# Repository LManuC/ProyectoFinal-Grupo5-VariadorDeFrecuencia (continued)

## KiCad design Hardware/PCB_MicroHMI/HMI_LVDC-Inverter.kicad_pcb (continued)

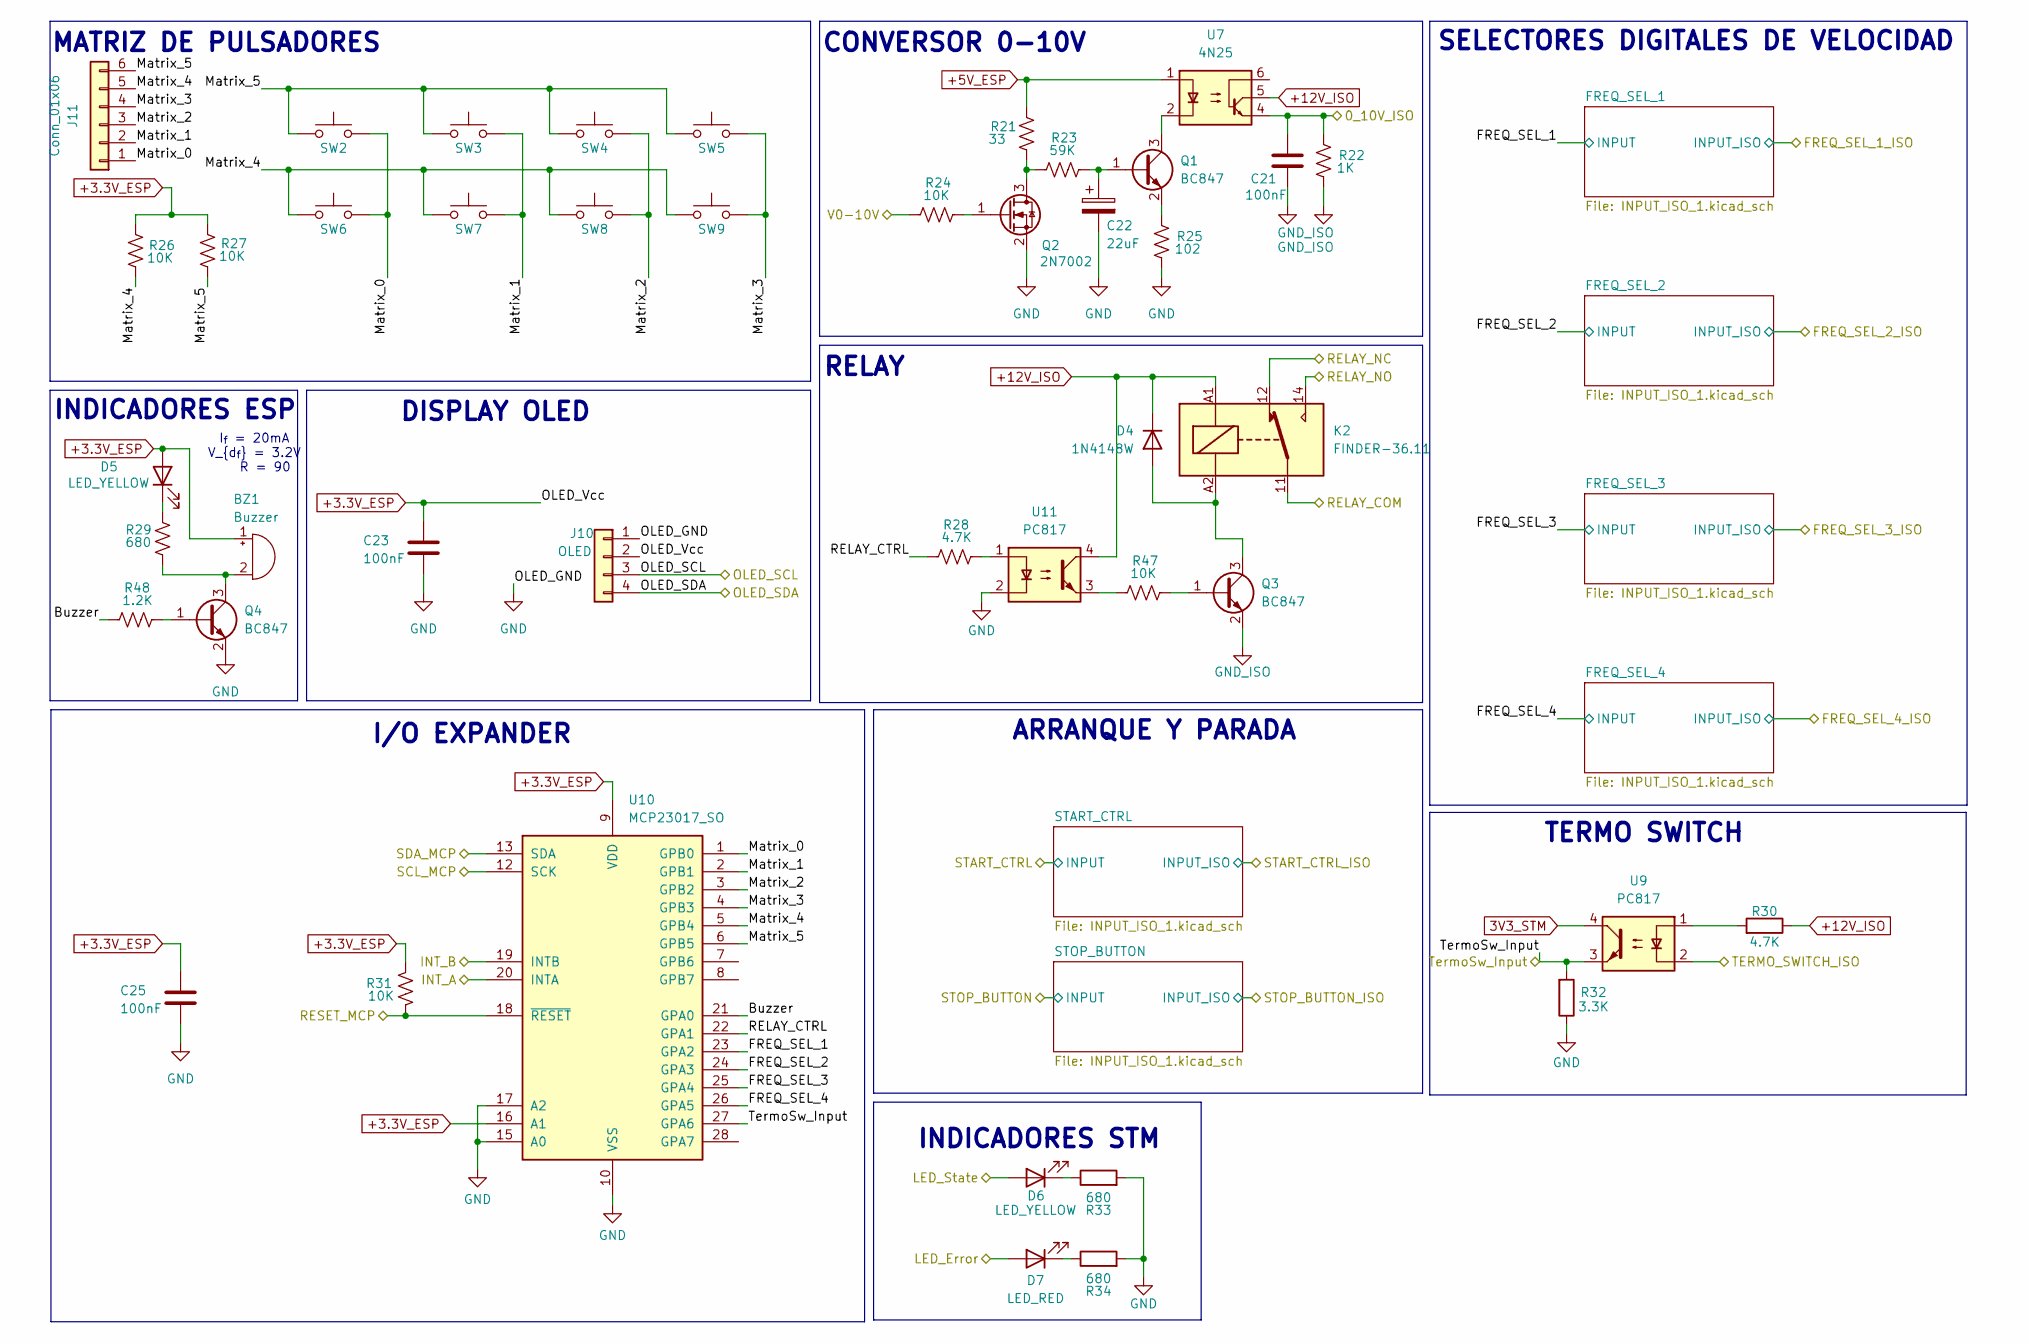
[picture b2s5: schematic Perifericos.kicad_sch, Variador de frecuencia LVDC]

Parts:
BZ1: Buzzer; Buzzer_12x9.5RM7.6
C21, C23, C25: 100nF; C_0603_1608Metric_Pad1.08x0.95mm_HandSolder
C22: 22uF; CP_Elec_5x5.4
D4: 1N4148W; D_SOD-123
D5, D6: LED_YELLOW; LED_0603_1608Metric_Pad1.05x0.95mm_HandSolder
D7: LED_RED; LED_0603_1608Metric_Pad1.05x0.95mm_HandSolder
J10: OLED; PinHeader_1x04_P2.54mm_Horizontal
J11: Conn_01x06; PinHeader_1x06_P2.54mm_Horizontal
K2: FINDER-36.11; Relay_SPDT_Finder_36.11
Q1, Q3, Q4: BC847; SOT-523
Q2: 2N7002; SOT-23
R21: 33; R_1210_3225Metric_Pad1.30x2.65mm_HandSolder
R22: 1K; R_0603_1608Metric_Pad0.98x0.95mm_HandSolder
R23: 59K; R_0603_1608Metric_Pad0.98x0.95mm_HandSolder
R24, R26, R27, R31, R47: 10K; R_0603_1608Metric_Pad0.98x0.95mm_HandSolder
R25: 102; R_0603_1608Metric_Pad0.98x0.95mm_HandSolder
R28, R30: 4.7K; R_0603_1608Metric_Pad0.98x0.95mm_HandSolder
R29, R33, R34: 680; R_0603_1608Metric_Pad0.98x0.95mm_HandSolder
R32: 3.3K; R_0603_1608Metric_Pad0.98x0.95mm_HandSolder
R48: 1.2K; R_0603_1608Metric_Pad0.98x0.95mm_HandSolder
SW2, SW3, SW4, SW5, SW6, SW7, SW8, SW9: SW_MEC_5G; SW_Push_SPST_NO_Alps_SKRK
U7: 4N25; DIP-6_W7.62mm_SMDSocket_SmallPads
U9, U11: PC817; DIP-4_W7.62mm_SMDSocket_SmallPads
U10: MCP23017_SO; SOIC-28W_7.5x17.9mm_P1.27mm

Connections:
3V3_STM: U9.4; also elsewhere on the board
+3.3V_ESP: BZ1.1 (+), C23.1, C25.1, D5.2 (A), J10.2, R26.1, R27.1, R31.1, U10.9 (VDD), U10.16 (A1); also elsewhere on the board
+5V_ESP: R21.2, U7.1; also elsewhere on the board
+12V_ISO: D4.1 (K), K2.A1, R30.1, U7.5, U11.4; also elsewhere on the board
/ESP32/INT_A: U10.20 (INTA); also elsewhere on the board
/ESP32/INT_B: U10.19 (INTB); also elsewhere on the board
/ESP32/OLED_SCL: J10.3; also elsewhere on the board
/ESP32/OLED_SDA: J10.4; also elsewhere on the board
/ESP32/RESET_MCP: R31.2, U10.18 (~RESET); also elsewhere on the board
/ESP32/SCL_MCP: U10.12 (SCK); also elsewhere on the board
/ESP32/SDA_MCP: U10.13 (SDA); also elsewhere on the board
/ESP32/V0-10V: R24.1; also elsewhere on the board
/Perifericos/0_10V_ISO: C21.1, R22.2, U7.4; also elsewhere on the board
/Perifericos/Buzzer: R48.1, U10.21 (GPA0)
/Perifericos/FREQ_SEL_1: U10.23 (GPA2); also elsewhere on the board
/Perifericos/FREQ_SEL_2: U10.24 (GPA3); also elsewhere on the board
/Perifericos/FREQ_SEL_3: U10.25 (GPA4); also elsewhere on the board
/Perifericos/FREQ_SEL_4: U10.26 (GPA5); also elsewhere on the board
/Perifericos/LED_Error: D7.2 (A); also elsewhere on the board
/Perifericos/LED_State: D6.2 (A); also elsewhere on the board
/Perifericos/Matrix_0: J11.1, SW2.2 (B), SW6.2 (B), U10.1 (GPB0)
/Perifericos/Matrix_1: J11.2, SW3.2 (B), SW7.2 (B), U10.2 (GPB1)
/Perifericos/Matrix_2: J11.3, SW4.2 (B), SW8.2 (B), U10.3 (GPB2)
/Perifericos/Matrix_3: J11.4, SW5.2 (B), SW9.2 (B), U10.4 (GPB3)
/Perifericos/Matrix_4: J11.5, R26.2, SW6.1 (A), SW7.1 (A), SW8.1 (A), SW9.1 (A), U10.5 (GPB4)
/Perifericos/Matrix_5: J11.6, R27.2, SW2.1 (A), SW3.1 (A), SW4.1 (A), SW5.1 (A), U10.6 (GPB5)
/Perifericos/RELAY_COM: K2.11; also elsewhere on the board
/Perifericos/RELAY_CTRL: R28.1, U10.22 (GPA1)
/Perifericos/RELAY_NC: K2.12; also elsewhere on the board
/Perifericos/RELAY_NO: K2.14; also elsewhere on the board
/Perifericos/TERMO_SWITCH_ISO: U9.2; also elsewhere on the board
/Perifericos/TermoSw_Input: R32.2, U9.3, U10.27 (GPA6); also elsewhere on the board
GND: C22.2, C23.2, C25.2, J10.1, Q2.2 (S), Q4.2 (E), R25.1, R32.1, R33.2, R34.2, U10.10 (VSS), U10.15 (A0), U10.17 (A2), U11.2; also elsewhere on the board
GND_ISO: C21.2, Q3.2 (E), R22.1; also elsewhere on the board
unnamed: BZ1.2 (-), Q4.3 (C), R29.2
unnamed: D4.2 (A), K2.A2, Q3.3 (C)
unnamed: D5.1 (K), R29.1
unnamed: D6.1 (K), R33.1
unnamed: D7.1 (K), R34.1
unnamed: C22.1, Q1.1 (B), R23.2
unnamed: Q1.3 (C), U7.2
unnamed: Q1.2 (E), R25.2
unnamed: Q2.3 (D), R21.1, R23.1
unnamed: Q2.1 (G), R24.2
unnamed: Q3.1 (B), R47.2
unnamed: Q4.1 (B), R48.2
unnamed: R28.2, U11.1
unnamed: R30.2, U9.1
unnamed: R47.1, U11.3

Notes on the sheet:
R = 90
I_{f} = 20mA V_{d_{f}} = 3.2V
RELAY
MATRIZ DE PULSADORES
ARRANQUE Y PARADA
INDICADORES STM
TERMO SWITCH
I/O EXPANDER
DISPLAY OLED
INDICADORES ESP
SELECTORES DIGITALES DE VELOCIDAD
CONVERSOR 0-10V

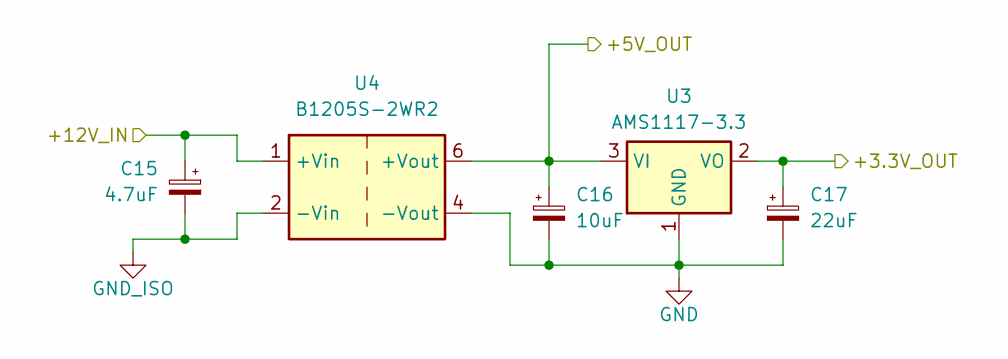
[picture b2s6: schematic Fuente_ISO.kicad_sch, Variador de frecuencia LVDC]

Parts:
C15: 4.7uF; C_0603_1608Metric
C16: 10uF; CP_Elec_4x5.4
C17: 22uF; CP_Elec_4x5.4
U3: AMS1117-3.3; SOT-223-3_TabPin2
U4: B1205S-2WR2; Converter_DCDC_TRACO_TMA-05xxS_12xxS_Single_THT

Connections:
3V3_STM: C17.1, U3.2 (VO); also elsewhere on the board
+12V_ISO: C15.1, U4.1 (+Vin); also elsewhere on the board
/Fuentes/Fuente_ISO/+5V_OUT: C16.1, U3.3 (VI), U4.6 (+Vout)
GND: C16.2, C17.2, U3.1 (GND), U4.4 (-Vout); also elsewhere on the board
GND_ISO: C15.2, U4.2 (-Vin); also elsewhere on the board

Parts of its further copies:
C18: 4.7uF; C_0603_1608Metric
C19: 10uF; CP_Elec_4x5.4
C20: 22uF; CP_Elec_4x5.4
U5: AMS1117-3.3; SOT-223-3_TabPin2
U6: B1205S-2WR2; Converter_DCDC_TRACO_TMA-05xxS_12xxS_Single_THT

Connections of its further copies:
+3.3V_ESP: C20.1, U5.2 (VO); also elsewhere on the board
+5V_ESP: C19.1, U5.3 (VI), U6.6 (+Vout); also elsewhere on the board
+12V_ISO: C18.1, U6.1 (+Vin); also elsewhere on the board
GND: C19.2, C20.2, U5.1 (GND), U6.4 (-Vout); also elsewhere on the board
GND_ISO: C18.2, U6.2 (-Vin); also elsewhere on the board

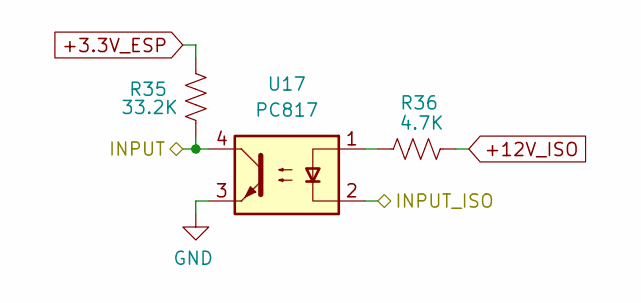
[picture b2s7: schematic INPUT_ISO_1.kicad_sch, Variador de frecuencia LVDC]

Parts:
R35: 33.2K; R_0603_1608Metric_Pad0.98x0.95mm_HandSolder
R36: 4.7K; R_0603_1608Metric_Pad0.98x0.95mm_HandSolder
U17: PC817; DIP-4_W7.62mm_SMDSocket_SmallPads

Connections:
+3.3V_ESP: R35.2; also elsewhere on the board
+12V_ISO: R36.2; also elsewhere on the board
/Perifericos/FREQ_SEL_1: R35.1, U17.4; also elsewhere on the board
/Perifericos/FREQ_SEL_1_ISO: U17.2; also elsewhere on the board
GND: U17.3; also elsewhere on the board
unnamed: R36.1, U17.1

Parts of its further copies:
R37, R39, R41, R43, R45: 33.2K; R_0603_1608Metric_Pad0.98x0.95mm_HandSolder
R38, R40, R42, R44, R46: 4.7K; R_0603_1608Metric_Pad0.98x0.95mm_HandSolder
U18, U19, U20, U21, U22: PC817; DIP-4_W7.62mm_SMDSocket_SmallPads

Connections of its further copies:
+3.3V_ESP: R37.2, R39.2, R41.2, R43.2, R45.2; also elsewhere on the board
+12V_ISO: R38.2, R40.2, R42.2, R44.2, R46.2; also elsewhere on the board
/ESP32/START_CTRL: R43.1, U21.4; also elsewhere on the board
/ESP32/STOP_BUTTON: R45.1, U22.4; also elsewhere on the board
/Perifericos/FREQ_SEL_2: R37.1, U18.4; also elsewhere on the board
/Perifericos/FREQ_SEL_2_ISO: U18.2; also elsewhere on the board
/Perifericos/FREQ_SEL_3: R39.1, U19.4; also elsewhere on the board
/Perifericos/FREQ_SEL_3_ISO: U19.2; also elsewhere on the board
/Perifericos/FREQ_SEL_4: R41.1, U20.4; also elsewhere on the board
/Perifericos/FREQ_SEL_4_ISO: U20.2; also elsewhere on the board
/Perifericos/START_CTRL_ISO: U21.2; also elsewhere on the board
/Perifericos/STOP_BUTTON_ISO: U22.2; also elsewhere on the board
GND: U18.3, U19.3, U20.3, U21.3, U22.3; also elsewhere on the board
unnamed: R38.1, U18.1
unnamed: R40.1, U19.1
unnamed: R42.1, U20.1
unnamed: R44.1, U21.1
unnamed: R46.1, U22.1

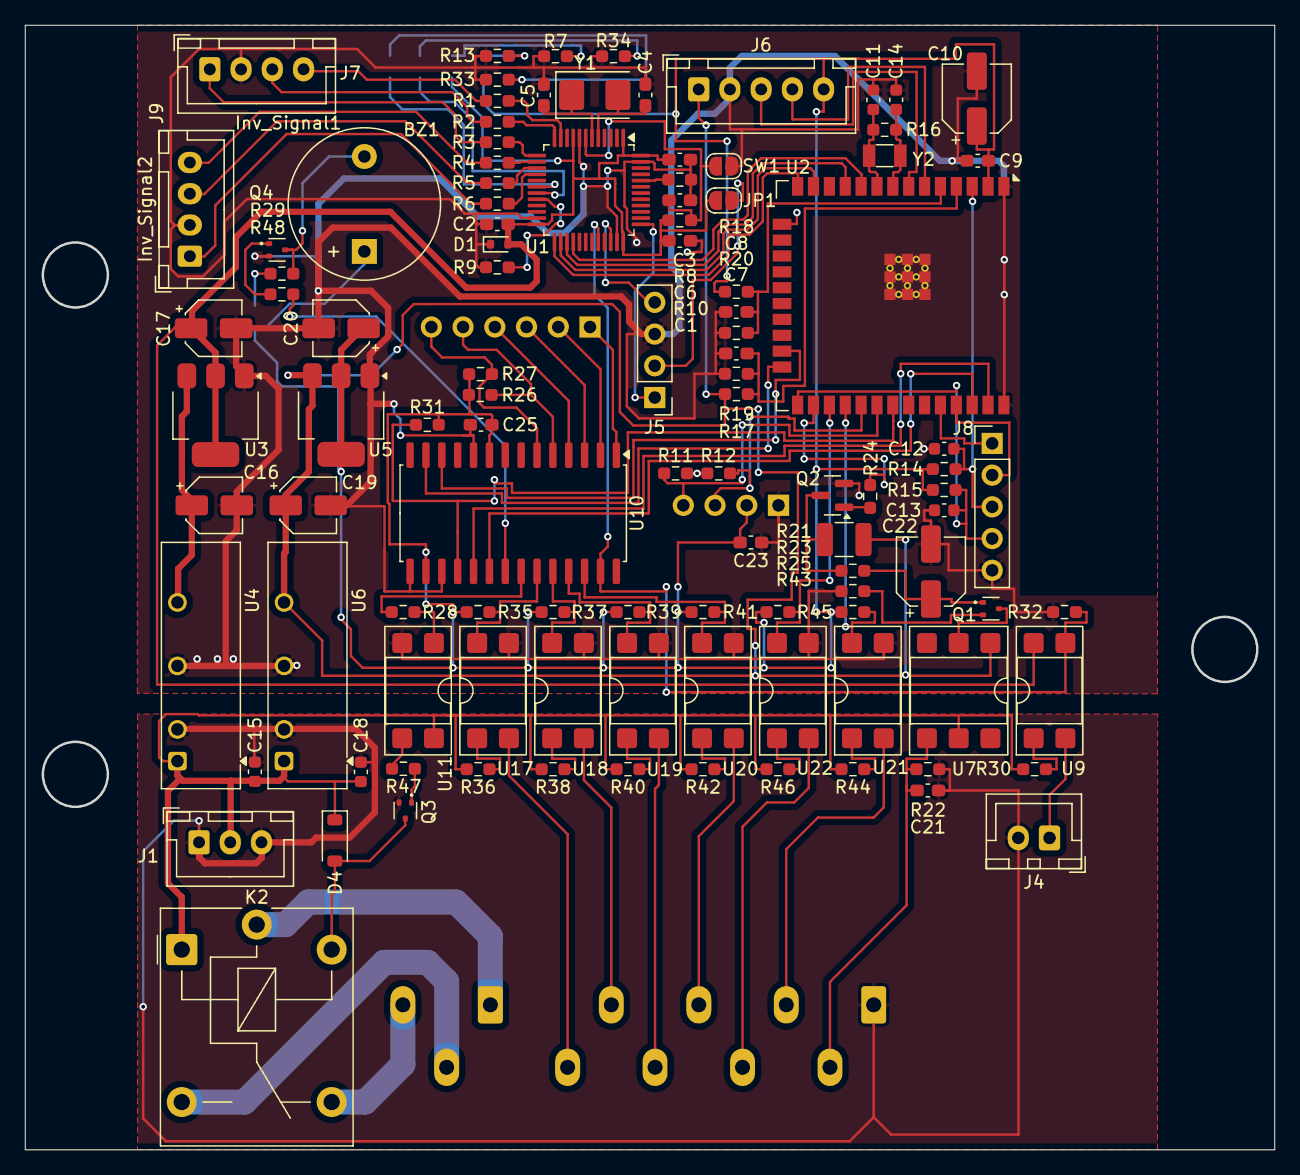
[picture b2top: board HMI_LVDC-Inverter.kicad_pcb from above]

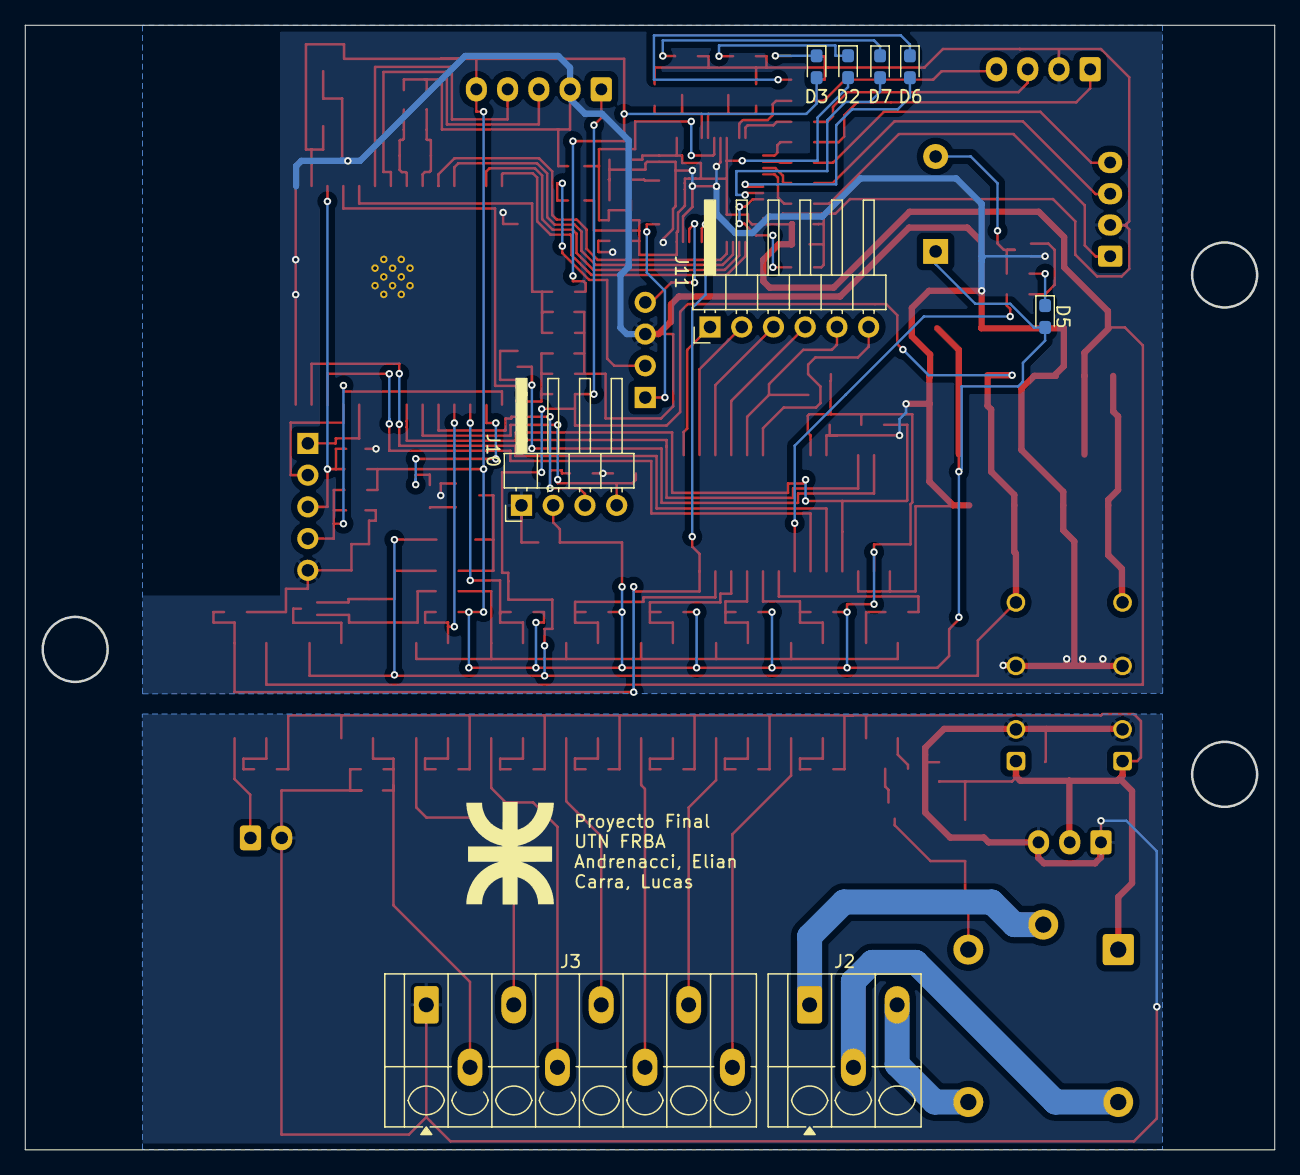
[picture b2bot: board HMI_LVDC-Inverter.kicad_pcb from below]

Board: 2 copper layers, 99.9 x 89.9 mm, 116 parts (9 on the bottom side), 100 nets.

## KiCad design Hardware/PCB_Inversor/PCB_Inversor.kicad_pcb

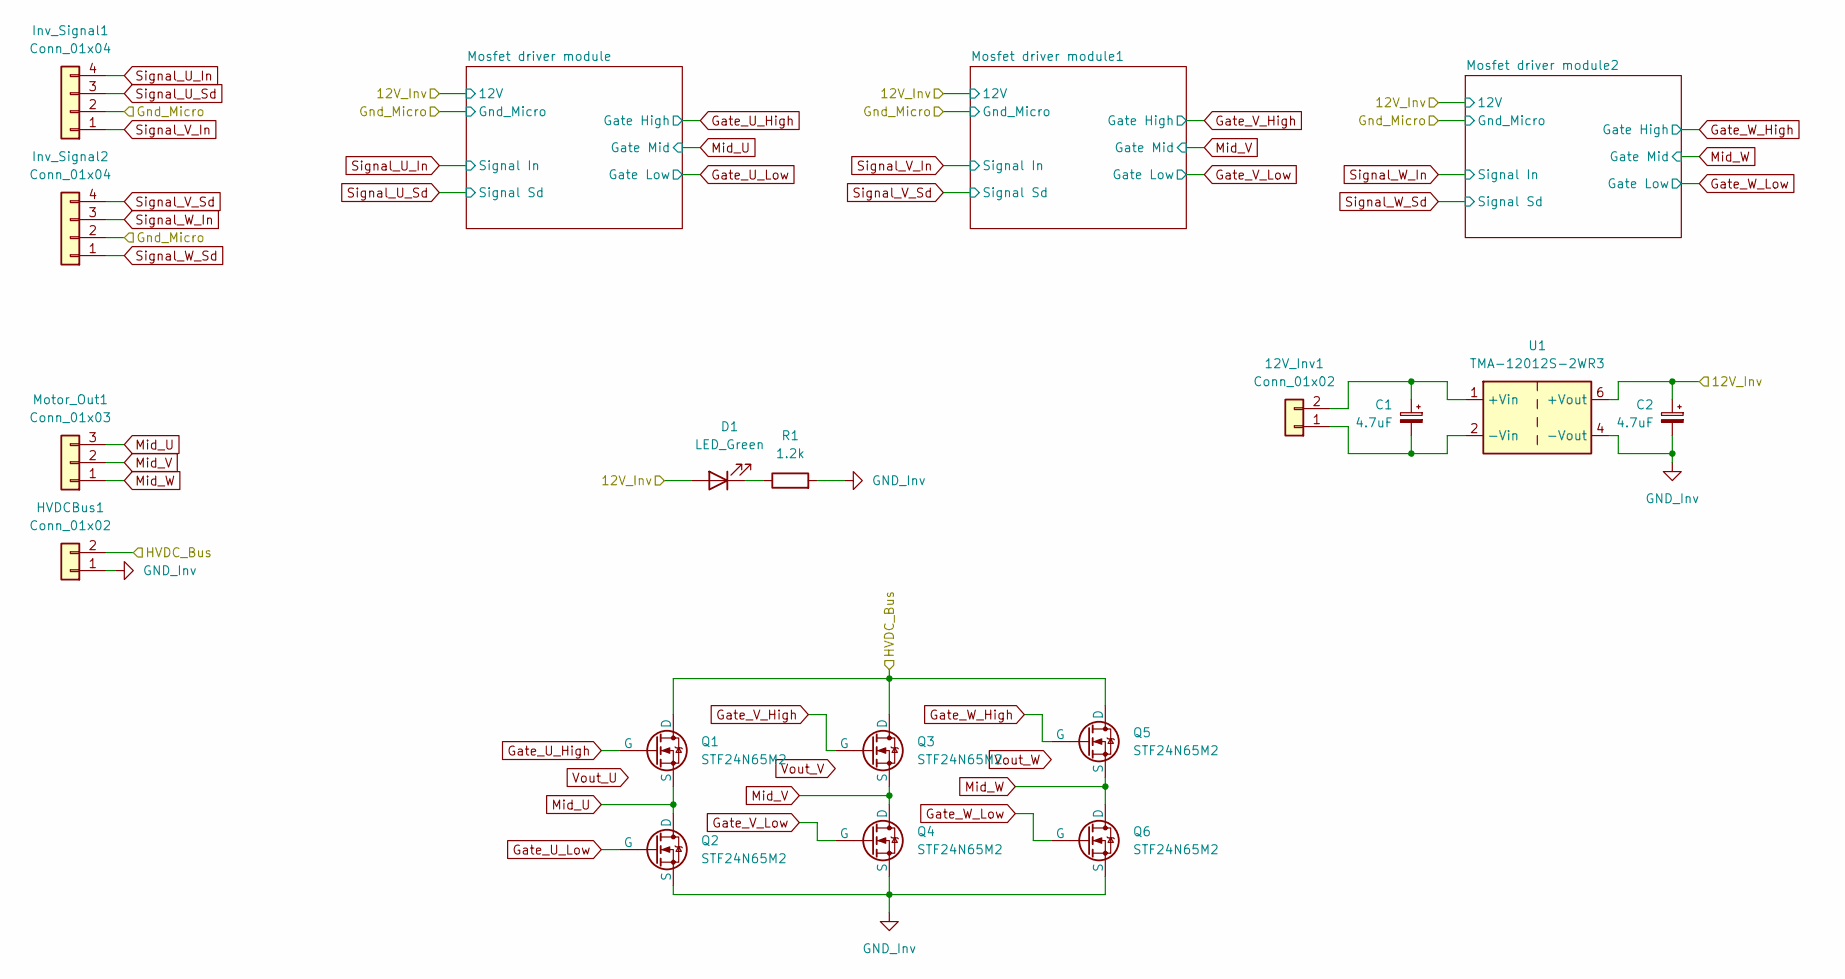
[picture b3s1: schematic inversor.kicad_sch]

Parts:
12V_Inv1: Conn_01x02; JST_XH_B2B-XH-A_1x02_P2.50mm_Vertical
C1, C2: 4.7uF; CP_Elec_4x5.4
D1: LED_Green; LED_0603_1608Metric_Pad1.05x0.95mm_HandSolder
HVDCBus1: Conn_01x02; PhoenixContact_MSTBVA_2,5_2-G-5,08_1x02_P5.08mm_Vertical
Inv_Signal1, Inv_Signal2: Conn_01x04; JST_XH_B4B-XH-A_1x04_P2.50mm_Vertical
Motor_Out1: Conn_01x03; PhoenixContact_MCV_1,5_3-G-5.08_1x03_P5.08mm_Vertical
Q1, Q2, Q3, Q4, Q5, Q6: STF24N65M2; TO-220-3_Horizontal_TabUp
R1: 1.2k; R_0603_1608Metric_Pad0.98x0.95mm_HandSolder
U1: TMA-12012S-2WR3; Converter_DCDC_TRACO_TMA-05xxS_12xxS_Single_THT

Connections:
/Inversor/12V_Inv: C2.1, D1.2 (A), U1.6 (+Vout); also elsewhere on the board
/Inversor/Gnd_Micro: Inv_Signal1.2, Inv_Signal2.2; also elsewhere on the board
/Inversor/HVDC_Bus: HVDCBus1.2, Q1.2 (D), Q3.2 (D), Q5.2 (D)
GND_Inv: C2.2, HVDCBus1.1, Q2.3 (S), Q4.3 (S), Q6.3 (S), R1.2, U1.4 (-Vout); also elsewhere on the board
Gate_U_High: Q1.1 (G); also elsewhere on the board
Gate_U_Low: Q2.1 (G); also elsewhere on the board
Gate_V_High: Q3.1 (G); also elsewhere on the board
Gate_V_Low: Q4.1 (G); also elsewhere on the board
Gate_W_High: Q5.1 (G); also elsewhere on the board
Gate_W_Low: Q6.1 (G); also elsewhere on the board
Mid_U: Motor_Out1.3, Q1.3 (S), Q2.2 (D); also elsewhere on the board
Mid_V: Motor_Out1.2, Q3.3 (S), Q4.2 (D); also elsewhere on the board
Mid_W: Motor_Out1.1, Q5.3 (S), Q6.2 (D); also elsewhere on the board
unnamed: 12V_Inv1.1, C1.2, U1.2 (-Vin)
unnamed: 12V_Inv1.2, C1.1, U1.1 (+Vin)
unnamed: D1.1 (K), R1.1
Signal_U_In: Inv_Signal1.4; also elsewhere on the board
Signal_U_Sd: Inv_Signal1.3; also elsewhere on the board
Signal_V_In: Inv_Signal1.1; also elsewhere on the board
Signal_V_Sd: Inv_Signal2.4; also elsewhere on the board
Signal_W_In: Inv_Signal2.3; also elsewhere on the board
Signal_W_Sd: Inv_Signal2.1; also elsewhere on the board

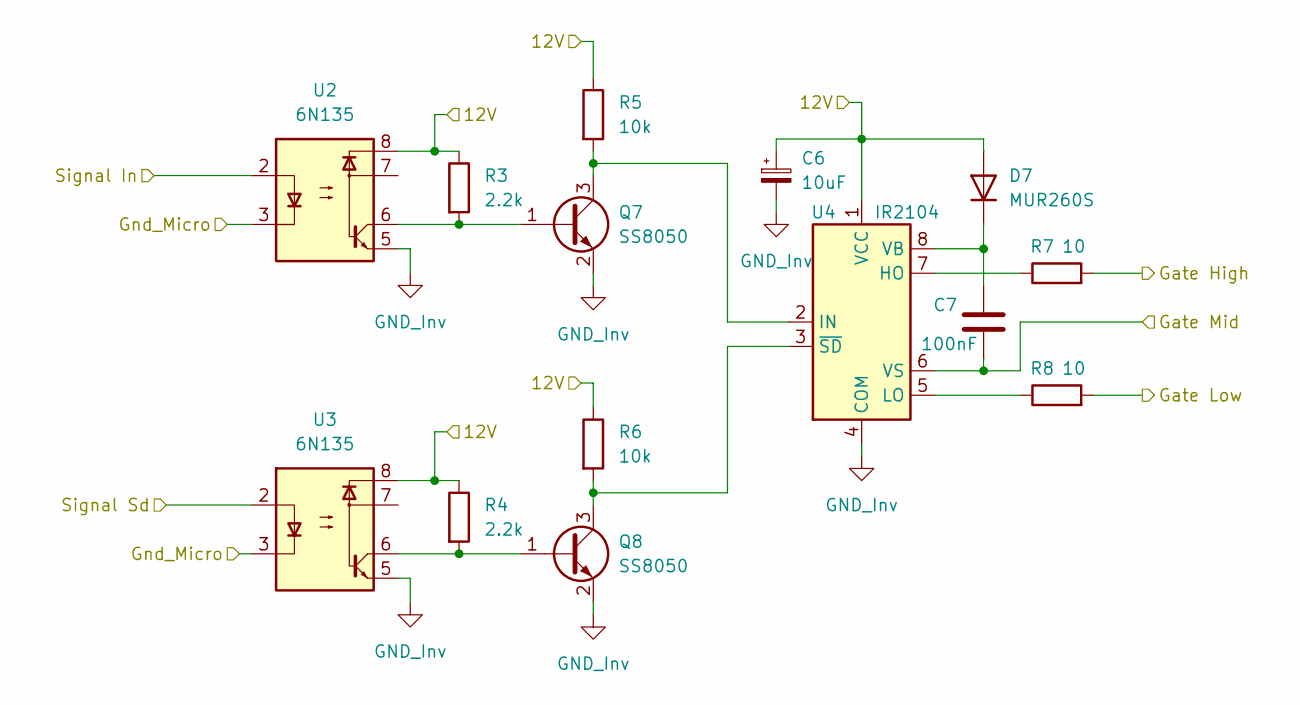
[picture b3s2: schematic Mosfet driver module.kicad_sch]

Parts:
C6: 10uF; CP_Elec_4x5.4
C7: 100nF; C_0603_1608Metric_Pad1.08x0.95mm_HandSolder
D7: MUR260S; D_SOD-523
Q7, Q8: SS8050; SOT-23
R3, R4: 2.2k; R_0603_1608Metric_Pad0.98x0.95mm_HandSolder
R5, R6: 10k; R_0603_1608Metric_Pad0.98x0.95mm_HandSolder
R7, R8: 10; R_0603_1608Metric_Pad0.98x0.95mm_HandSolder
U2, U3: 6N135; SOP-8_6.62x9.15mm_P2.54mm
U4: IR2104; SOIC-8_3.9x4.9mm_P1.27mm

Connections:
/Inversor/12V_Inv: C6.1, D7.2 (A), R3.1, R4.1, R5.1, R6.1, U2.8, U3.8, U4.1 (VCC); also elsewhere on the board
/Inversor/Gnd_Micro: U2.3, U3.3; also elsewhere on the board
GND_Inv: C6.2, Q7.2 (E), Q8.2 (E), U2.5, U3.5, U4.4 (COM); also elsewhere on the board
Gate_U_High: R7.2; also elsewhere on the board
Gate_U_Low: R8.2; also elsewhere on the board
Mid_U: C7.2, U4.6 (VS); also elsewhere on the board
unnamed: C7.1, D7.1 (K), U4.8 (VB)
unnamed: Q7.1 (B), R3.2, U2.6
unnamed: Q7.3 (C), R5.2, U4.2 (IN)
unnamed: Q8.1 (B), R4.2, U3.6
unnamed: Q8.3 (C), R6.2, U4.3 (~SD)
unnamed: R7.1, U4.7 (HO)
unnamed: R8.1, U4.5 (LO)
Signal_U_In: U2.2; also elsewhere on the board
Signal_U_Sd: U3.2; also elsewhere on the board

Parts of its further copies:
C8, C10: 10uF; CP_Elec_4x5.4
C9, C11: 100nF; C_0603_1608Metric_Pad1.08x0.95mm_HandSolder
D8, D9: MUR260S; D_SOD-523
Q9, Q10, Q11, Q12: SS8050; SOT-23
R9, R10, R15, R16: 2.2k; R_0603_1608Metric_Pad0.98x0.95mm_HandSolder
R11, R12, R17, R18: 10k; R_0603_1608Metric_Pad0.98x0.95mm_HandSolder
R13, R14, R19, R20: 10; R_0603_1608Metric_Pad0.98x0.95mm_HandSolder
U5, U6, U8, U9: 6N135; SOP-8_6.62x9.15mm_P2.54mm
U7, U10: IR2104; SOIC-8_3.9x4.9mm_P1.27mm

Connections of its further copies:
/Inversor/12V_Inv: C8.1, C10.1, D8.2 (A), D9.2 (A), R9.1, R10.1, R11.1, R12.1, R15.1, R16.1, R17.1, R18.1, U5.8, U6.8, U7.1 (VCC), U8.8, U9.8, U10.1 (VCC); also elsewhere on the board
/Inversor/Gnd_Micro: U5.3, U6.3, U8.3, U9.3; also elsewhere on the board
GND_Inv: C8.2, C10.2, Q9.2 (E), Q10.2 (E), Q11.2 (E), Q12.2 (E), U5.5, U6.5, U7.4 (COM), U8.5, U9.5, U10.4 (COM); also elsewhere on the board
Gate_V_High: R13.2; also elsewhere on the board
Gate_V_Low: R14.2; also elsewhere on the board
Gate_W_High: R19.2; also elsewhere on the board
Gate_W_Low: R20.2; also elsewhere on the board
Mid_V: C9.2, U7.6 (VS); also elsewhere on the board
Mid_W: C11.2, U10.6 (VS); also elsewhere on the board
unnamed: C9.1, D8.1 (K), U7.8 (VB)
unnamed: C11.1, D9.1 (K), U10.8 (VB)
unnamed: Q9.1 (B), R9.2, U5.6
unnamed: Q9.3 (C), R11.2, U7.2 (IN)
unnamed: Q10.1 (B), R10.2, U6.6
unnamed: Q10.3 (C), R12.2, U7.3 (~SD)
unnamed: Q11.1 (B), R15.2, U8.6
unnamed: Q11.3 (C), R17.2, U10.2 (IN)
unnamed: Q12.1 (B), R16.2, U9.6
unnamed: Q12.3 (C), R18.2, U10.3 (~SD)
unnamed: R13.1, U7.7 (HO)
unnamed: R14.1, U7.5 (LO)
unnamed: R19.1, U10.7 (HO)
unnamed: R20.1, U10.5 (LO)
Signal_V_In: U5.2; also elsewhere on the board
Signal_V_Sd: U6.2; also elsewhere on the board
Signal_W_In: U8.2; also elsewhere on the board
Signal_W_Sd: U9.2; also elsewhere on the board

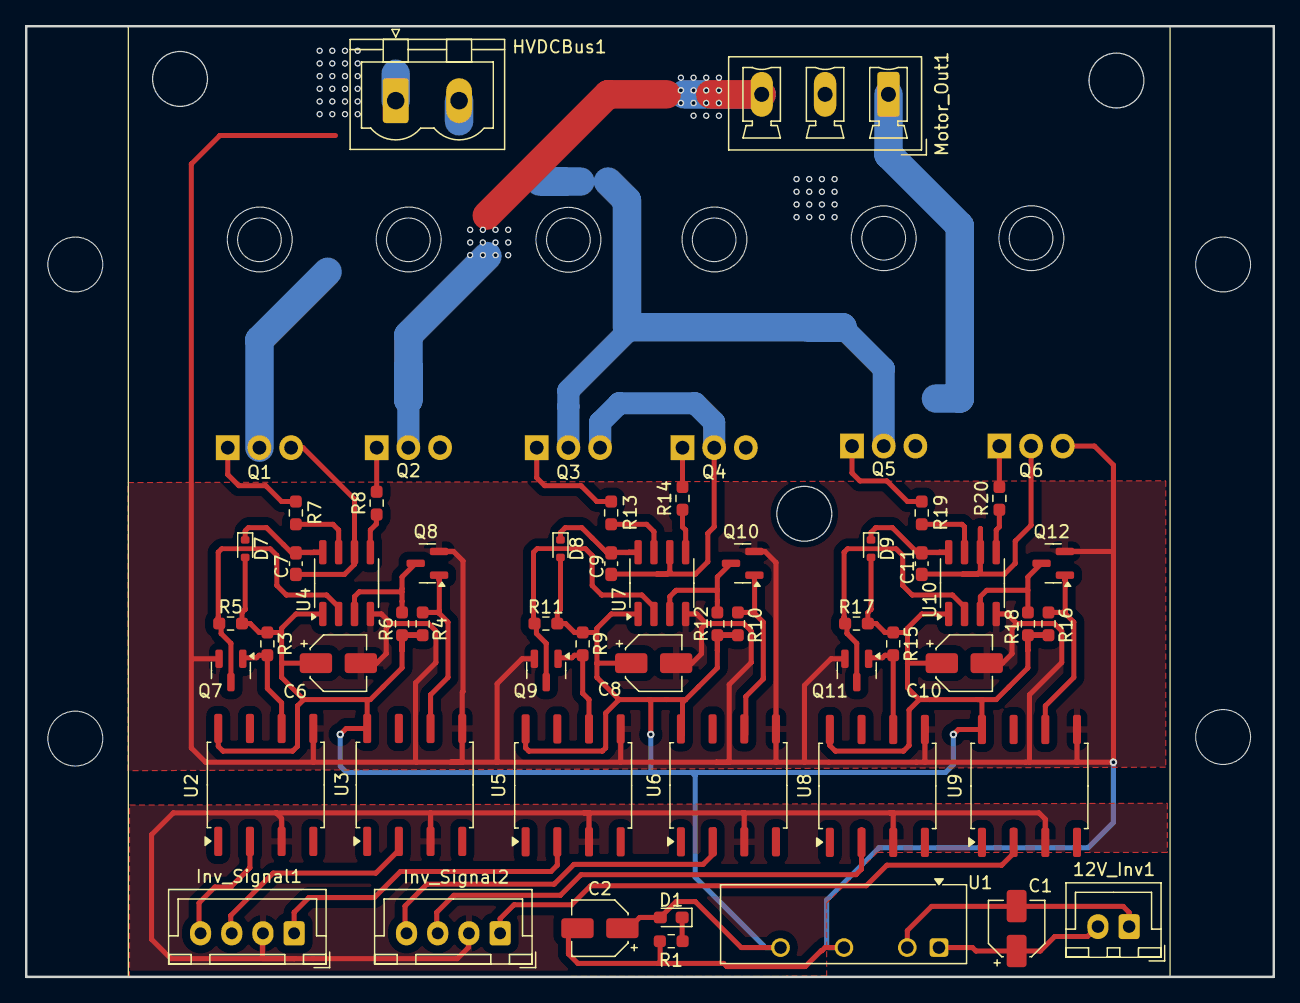
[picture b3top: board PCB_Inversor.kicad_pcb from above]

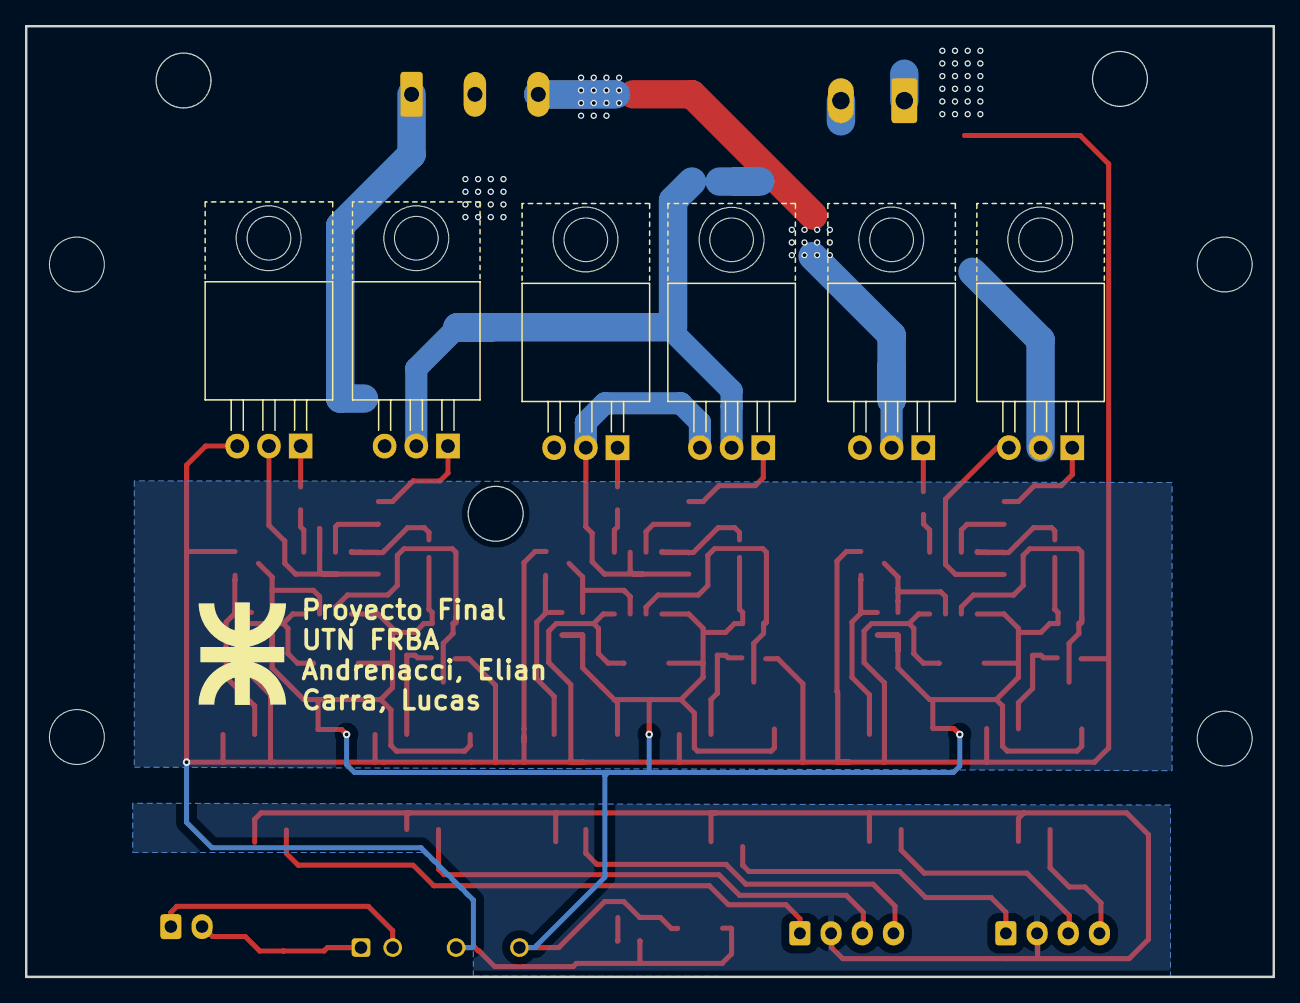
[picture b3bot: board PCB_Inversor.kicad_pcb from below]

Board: 2 copper layers, 100.0 x 76.2 mm, 58 parts (6 on the bottom side), 43 nets.

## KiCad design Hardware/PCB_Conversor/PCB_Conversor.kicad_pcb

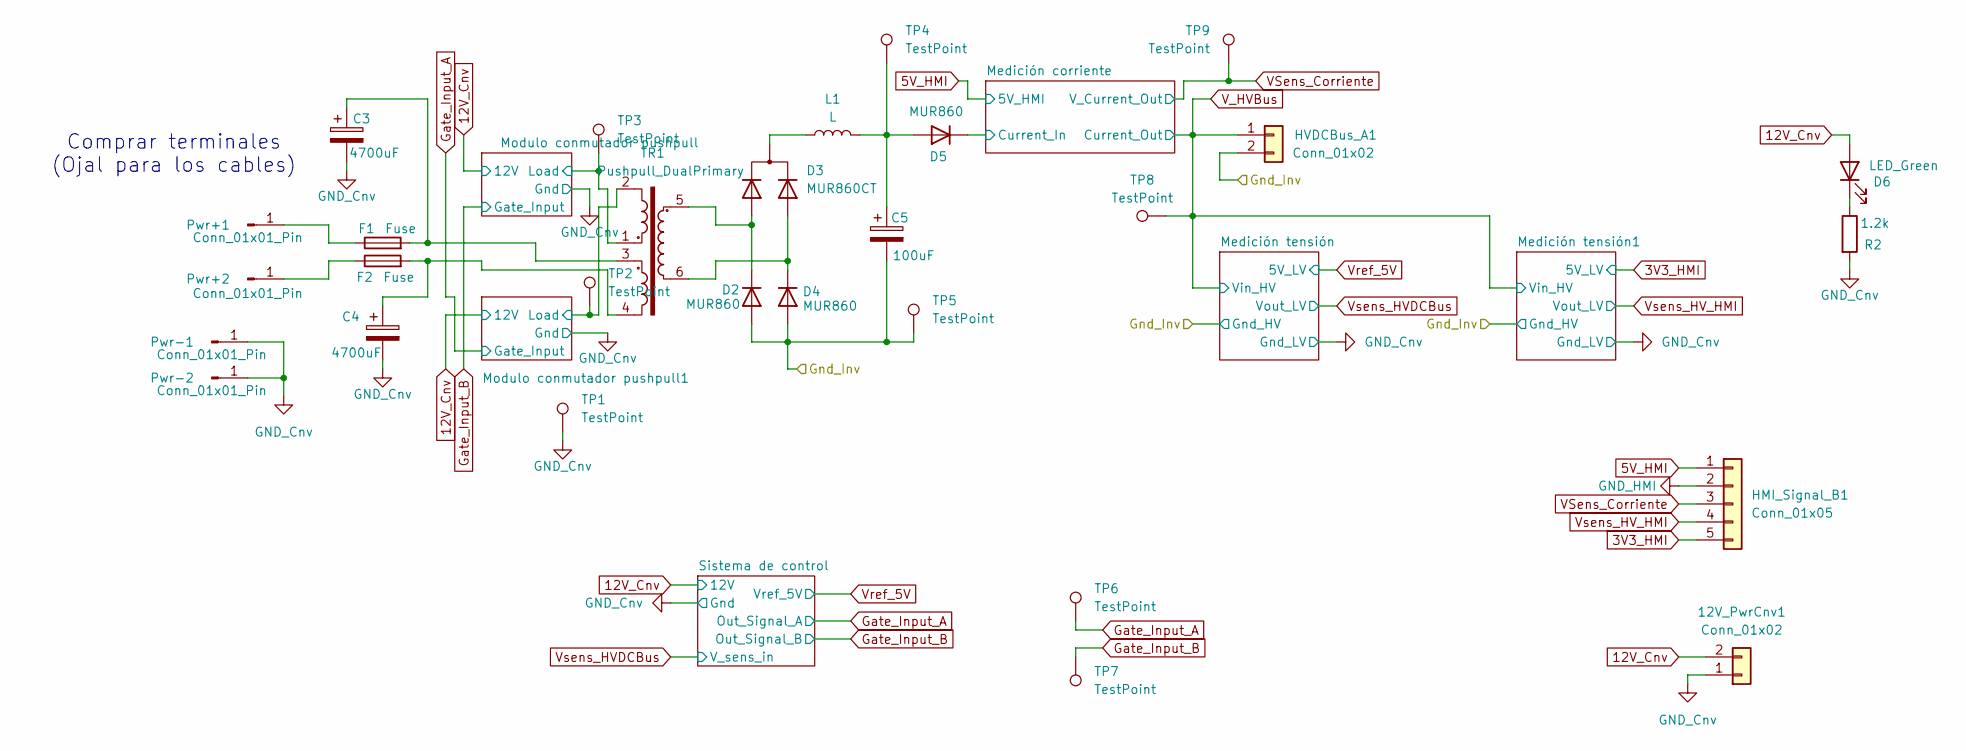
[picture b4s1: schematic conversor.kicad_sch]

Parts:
12V_PwrCnv1: Conn_01x02; JST_XH_B2B-XH-A_1x02_P2.50mm_Vertical
C3, C4: 4700uF; CP_Radial_D16.0mm_P7.50mm
C5: 100uF; CP_Radial_D22.0mm_P10.00mm_SnapIn
D2, D4, D5: MUR860; TO-220-2_Horizontal_TabUp
D3: MUR860CT; TO-220-3_Horizontal_TabUp
D6: LED_Green; LED_0603_1608Metric_Pad1.05x0.95mm_HandSolder
F1, F2: Fuse; Fuse Holder XF-509P
HMI_Signal_B1: Conn_01x05; JST_XH_B5B-XH-A_1x05_P2.50mm_Vertical
HVDCBus_A1: Conn_01x02; PhoenixContact_MSTBVA_2,5_2-G-5,08_1x02_P5.08mm_Vertical
L1: L; L_Toroid_Vertical_L21.6mm_W8.4mm_P8.38mm_Pulse_G
Pwr+1, Pwr+2: Conn_01x01_Pin; 5mm cable solder join
Pwr-1, Pwr-2: Conn_01x01_Pin; 5mm cable solder join
R2: 1.2k; R_0603_1608Metric_Pad0.98x0.95mm_HandSolder
TP1, TP2, TP3, TP4, TP5, TP6, TP7, TP8, TP9: TestPoint; TestPoint_Loop_D2.60mm_Drill1.6mm_Beaded
TR1: Pushpull_DualPrimary; EDT36 11

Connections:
3V3_HMI: HMI_Signal_B1.5; also elsewhere on the board
5V_HMI: HMI_Signal_B1.1; also elsewhere on the board
12V_Cnv: 12V_PwrCnv1.2, D6.2 (A); also elsewhere on the board
/Conversor/Gnd_Inv: C5.2, D2.2 (A), D4.2 (A), HVDCBus_A1.2, TP5.1; also elsewhere on the board
/Conversor/Medición corriente/Current_In: D5.1 (K); also elsewhere on the board
/Conversor/Modulo conmutador pushpull1/Load: TP2.1, TR1.2; also elsewhere on the board
/Conversor/Modulo conmutador pushpull/Load: TP3.1, TR1.1; also elsewhere on the board
GND_Cnv: 12V_PwrCnv1.1, C3.2, C4.2, Pwr-1.1, Pwr-2.1, R2.2, TP1.1; also elsewhere on the board
GND_HMI: HMI_Signal_B1.2; also elsewhere on the board
Gate_Input_A: TP6.1; also elsewhere on the board
Gate_Input_B: TP7.1; also elsewhere on the board
unnamed: C3.1, F1.2, TR1.3
unnamed: C4.1, F2.2, TR1.4
unnamed: D2.1 (K), D3.1 (A1), TR1.5
unnamed: D3.3 (A2), D4.1 (K), TR1.6
unnamed: D3.2 (K), L1.1
unnamed: C5.1, D5.2 (A), L1.2, TP4.1
unnamed: D6.1 (K), R2.1
unnamed: F1.1, Pwr+1.1
unnamed: F2.1, Pwr+2.1
VSens_Corriente: HMI_Signal_B1.3, TP9.1; also elsewhere on the board
V_HVBus: HVDCBus_A1.1, TP8.1; also elsewhere on the board
Vsens_HV_HMI: HMI_Signal_B1.4; also elsewhere on the board

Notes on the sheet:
Comprar terminales (Ojal para los cables)
